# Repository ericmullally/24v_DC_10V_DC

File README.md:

## Simple 24V to 10V step down switching power supply.
Board built using 926-LM3150MH/NOPB by Texas insturments.

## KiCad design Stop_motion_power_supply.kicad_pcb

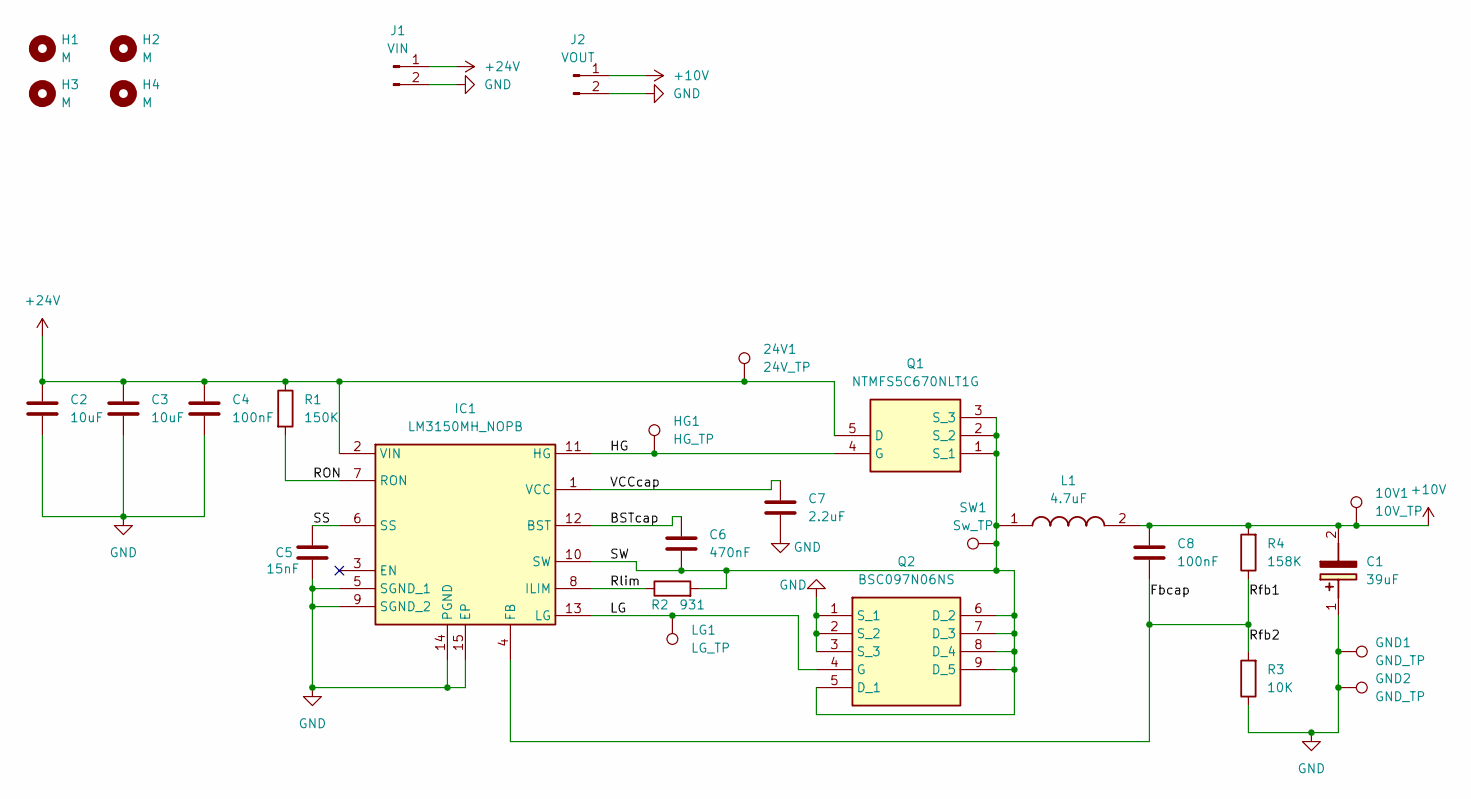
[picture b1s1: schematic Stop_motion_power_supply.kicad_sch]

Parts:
10V1: 10V_TP; TestPoint_Pad_D2.0mm
24V1: 24V_TP; TestPoint_Pad_D2.0mm
C1: 39uF; 16SVF82M; Mouser Part Number 667-16SVPC39MV
C2, C3: 10uF; C_1210_3225Metric_Pad1.33x2.70mm_HandSolder
C4, C8: 100nF; C_0805_2012Metric_Pad1.18x1.45mm_HandSolder
C5: 15nF; C_0805_2012Metric_Pad1.18x1.45mm_HandSolder
C6: 470nF; C_0805_2012Metric_Pad1.18x1.45mm_HandSolder
C7: 2.2uF; C_0805_2012Metric_Pad1.18x1.45mm_HandSolder
GND1, GND2: GND_TP; TestPoint_Pad_D2.0mm
H1, H2, H3, H4: M; MountingHole_3.2mm_M3
HG1: HG_TP; TestPoint_Pad_D2.0mm
IC1: LM3150MH_NOPB; SOP65P640X110-15N; Mouser Part Number 926-LM3150MH/NOPB
J1: VIN; PinHeader_1x02_P2.54mm_Vertical
J2: VOUT; PinHeader_1x02_P2.54mm_Vertical
L1: 4.7uF; INDPM132129X640N; Mouser Part Number 70-IHLP5050FDER4R7M1
LG1: LG_TP; TestPoint_Pad_D2.0mm
Q1: NTMFS5C670NLT1G; NRVTS10100EMFST1G; Mouser Part Number 863-NTMFS5C670NLT1G
Q2: BSC097N06NS; Mouser Part Number 726-BSC097N06NS
R1: 150K; R_0805_2012Metric_Pad1.20x1.40mm_HandSolder
R2: 931; R_0805_2012Metric_Pad1.20x1.40mm_HandSolder
R3: 10K; R_0805_2012Metric_Pad1.20x1.40mm_HandSolder
R4: 158K; R_0805_2012Metric_Pad1.20x1.40mm_HandSolder
SW1: Sw_TP; TestPoint_Pad_D2.0mm

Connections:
+10V: 10V1.1, C1.2 (-), C8.1, J2.1, L1.2, R4.2
+24V: 24V1.1, C2.1, C3.1, C4.1, IC1.2 (VIN), J1.1, Q1.5 (D), R1.1
/BSTcap: C6.1, IC1.12 (BST)
/Fbcap: C8.2, IC1.4 (FB), R3.2, R4.1
/HG: HG1.1, IC1.11 (HG), Q1.4 (G)
/LG: IC1.13 (LG), LG1.1, Q2.4 (G)
/RON: IC1.7 (RON), R1.2
/Rlim: IC1.8 (ILIM), R2.1
/SS: C5.1, IC1.6 (SS)
/SW: C6.2, IC1.10 (SW), L1.1, Q1.1 (S_1), Q1.2 (S_2), Q1.3 (S_3), Q2.5 (D_1), Q2.6 (D_2), Q2.7 (D_3), Q2.8 (D_4), Q2.9 (D_5), R2.2, SW1.1
/VCCcap: C7.1, IC1.1 (VCC)
GND: C1.1 (+), C2.2, C3.2, C4.2, C5.2, C7.2, GND1.1, GND2.1, IC1.5 (SGND_1), IC1.9 (SGND_2), IC1.14 (PGND), IC1.15 (EP), J1.2, J2.2, Q2.1 (S_1), Q2.2 (S_2), Q2.3 (S_3), R3.1

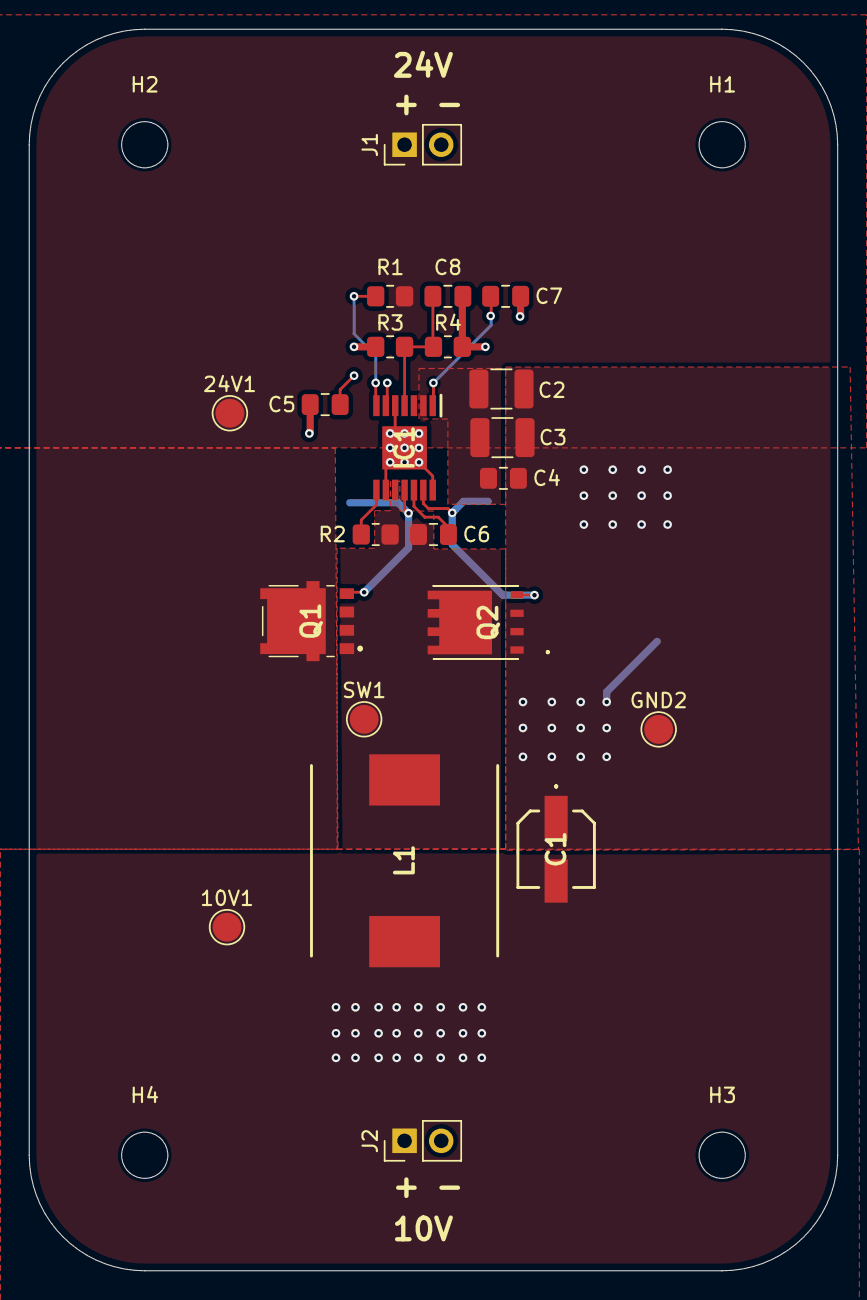
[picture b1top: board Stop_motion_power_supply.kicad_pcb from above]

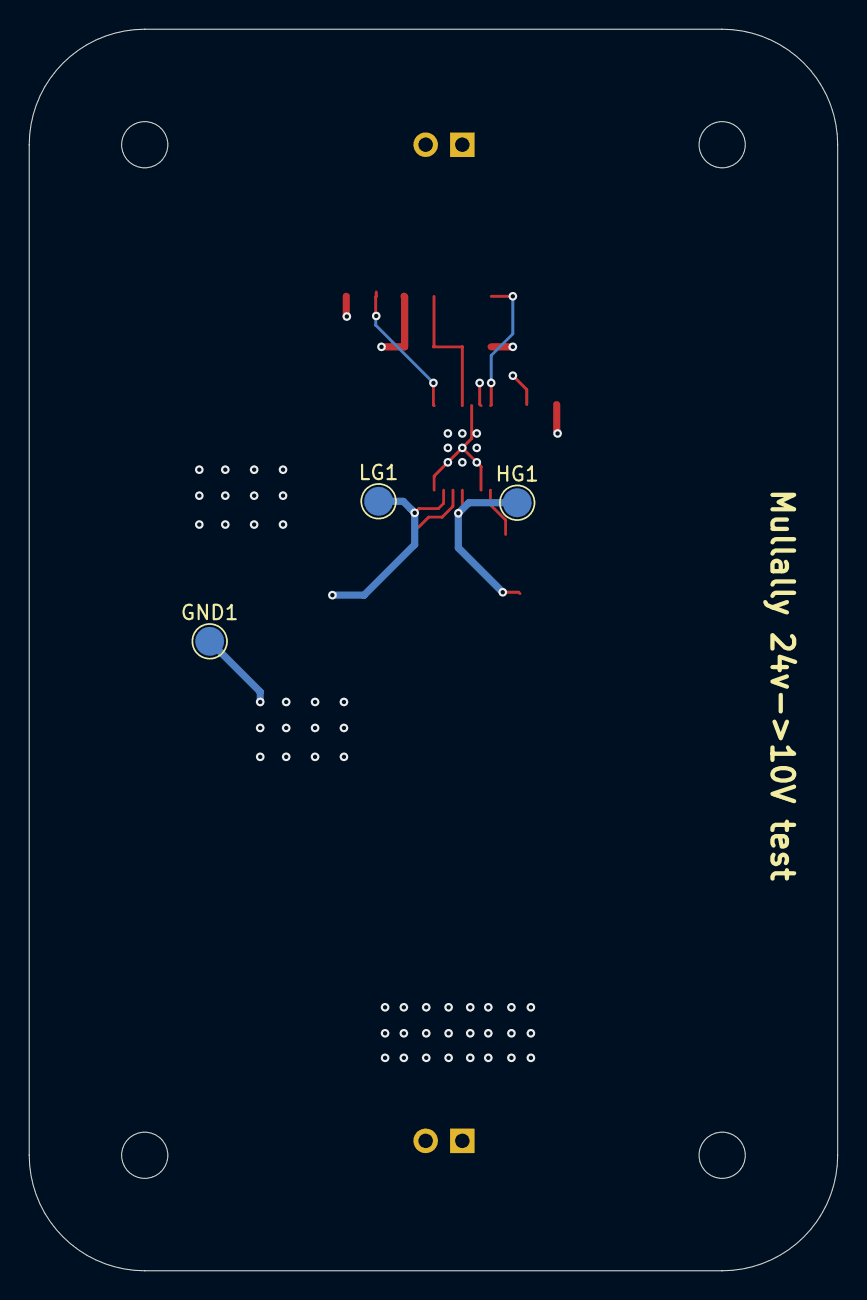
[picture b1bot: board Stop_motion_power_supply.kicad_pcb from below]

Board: 4 copper layers, 56.0 x 86.0 mm, 29 parts (3 on the bottom side), 12 nets.

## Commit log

2025-08-06 finished, saved for future needs.
2025-08-06 Create LICENSE
